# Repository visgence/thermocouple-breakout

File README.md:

The K-Type thermocouple conditioner is an easy way to use a K-Type thermocouple with an Arduino or other microcontrollers. At its heart is a AD595 thermocouple conditioner IC. The AD595 is laser trimmed for accuracy and performs automatic cold-junction compensation, which means you can just drop it into a project and get accurate results right away.

We created the K-Type Thermocouple Conditioner board while rebuilding our reflow toaster oven. The original controller used an AD595 and we were happy with its results. Since the toaster oven is a semi-permanent setup, we gave the board screw terminals and holes for robust mounting.

#### Specs
- [AD595A](http://www.analog.com/static/imported-files/data_sheets/AD594_595.pdf) laser trimmed for K-type thermocouple and 3 degree C basic accuracy
- 10mV / K output, easy to read with any ADC
- K-type input fits standard probes
- Alarm output and LED signals that probe is disconnected
- Screw terminals and mounting holes for easy long-term mounting

#### Use with an Arduino
We built our thermocouple conditioner specifically to use with Arduino and compatible boards. See the [example sketch](https://github.com/visgence/thermocouple-breakout/tree/master/example_code/thermocouple_conditioner_arduino) for a simple example.

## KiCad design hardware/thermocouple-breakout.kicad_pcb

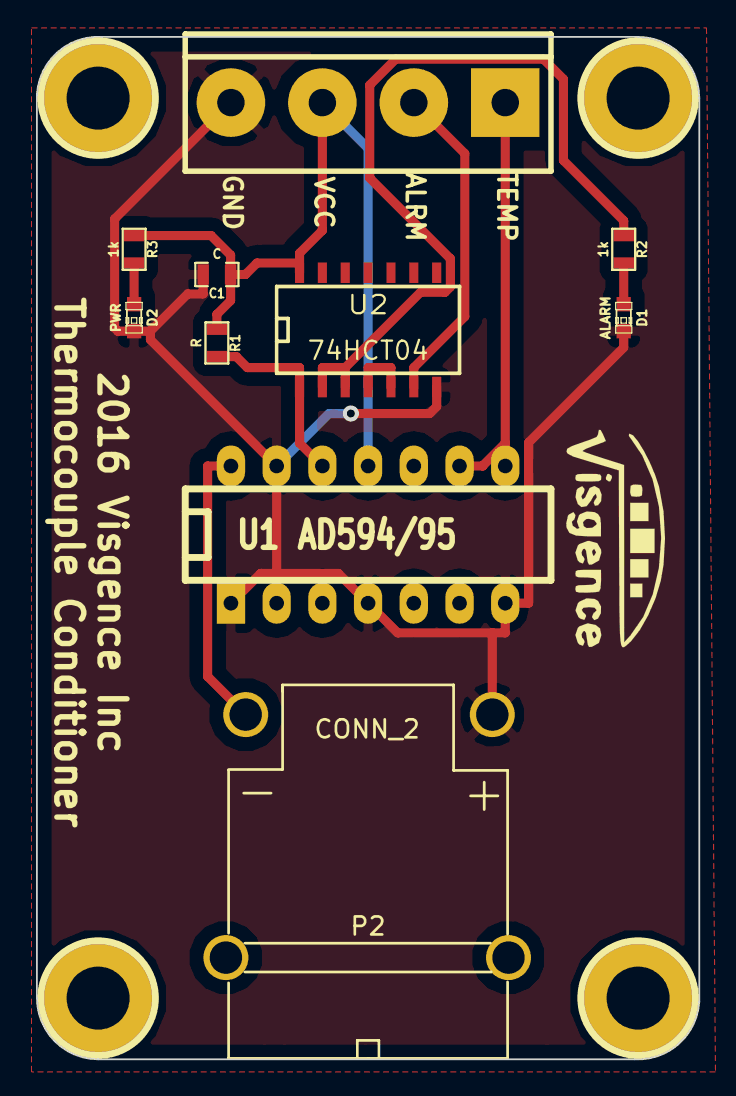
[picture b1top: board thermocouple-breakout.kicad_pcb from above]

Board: 2 copper layers, 36.8 x 56.8 mm, 14 parts (0 on the bottom side), 10 nets.

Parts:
C1: C; SM0603_Capa_VIS
D1: ALARM; LED-0603
D2: PWR; LED-0603
P1: CONN_4; bornier4
P2: CONN_2; PCC-SMP
R1: R; SM0603_VIS
R2, R3: 1k; SM0603_VIS
U1: AD594/95; DIP-14__300_ELL
U2: 74HCT04; SO14N
h1, h2, h3, h4: pin; 1pin_C

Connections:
ALARM: P1.2, U2.6
GND: C1.2, D1.2, D2.2, P1.4, P2.1, U1.1, U1.4, U1.7, U1.13, U2.7
unnamed: D1.1, R2.2
unnamed: D2.1, R3.2
unnamed: P2.2, U1.14
unnamed: R1.2, U1.12, U2.1
unnamed: R2.1, U2.2, U2.3
unnamed: U2.4, U2.5
TEMP: P1.1, U1.8, U1.9
VCC: C1.1, P1.3, R1.1, R3.1, U1.11, U2.14

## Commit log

2014-10-16 moved pcb files to their own folder
2014-10-16 adds an example arduino sketch
2014-10-16 adds README
2016-05-21 Updated to kicad 4.0.2
2016-05-25 Began work on thermocouple layout. Began modeling custom pieces.
2016-05-26 Finished thermocouple board in KiCad
2016-05-26 Finishing up the termalcouple, exported JSON to 3dview repo.
